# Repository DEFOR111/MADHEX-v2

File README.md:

# ***MADHEX-v2***
> ## the Fully open source 6 legged hexapod robot 

* Custom controller PCB
* Fully open-source
* great mechanics design with amortization
#### the 18DOF hexapod robot 

## the README include 
* Overwiew
* Features
* Electronics
* CAD
* firmware
* BOM

# Overview 
MadHex v2 is an open-source hexapod robot designed for people who wanna build their spider friend and learn building — CAD, PCB , and design  are all custom-made. This repository contains everything needed to reproduce the robot: CAD source and manufacturing files, PCB design and production files, bill of materials

Currently the project is in procces of building 

# Features

* Fully custom mechanical design , all parts are 3d printable
* custom control PCB : schematics , 4 layer of layout , kicad project , and manufactoring files
* 2 Full BOM files for both PCB and Robot
* great design with beatiful decisions

 # Electronics PCB 
 ### The schematics 

### the renders

Custom 4-layer control board 

**Key Features :**

* **MCU:** ESP32-S3-WROOM-1 — great wifi/bluetooth MCU 
* **IMU:** BNO055  — 9-DOF orientation for balancing
* **Power input:** XT60 connector - for battery connection 
* **Power protection:** low-side N-MOSFET reverse-polarity protection NTMFS5C404NL + SMBJ10CA TVS diode + 30A fuse
* **Regulation:** two TPS563201 buck converters: battery → 5.3V → Schottky → 5V rail → 3.3V
* **USB power path:** Schottky diodes keep USB and the battery side separated
* **Power monitoring:** INA226 current/voltage sensor (I2C) with a 2m shunt + analog voltage divider as backup 
* **USB-C:**  USB with USBLC6-2P6 ESD protection
* **Status LED:**  WS2812 RGB
* **Servo interface:** 2× independent half-duplex UART buses , 3 legs per bus — driving serial bus servos over a single data line per bus instead of  PWM channels
* **Connectors:** 6 3-pin leg connectors (J2–J7), one per leg makes the wiring a lot easier 

**Files:**
* Schematic: [download the schematics](Electronics/Hexapod%20PCB%202.pdf)
* Gerbers + drill files : [Download the manufactoring files](Electronics/manufactoring%20files.zip)
* BOM: [download the PCB BOM](BOM-PCB.csv)

**Board spec:**

| Spec | Value |
|---|---|
| Layers | 4 |
| MCU | ESP32-S3-WROOM-1 |
| Logic  | 3.3V |
| Peripheral  | 5V |
| Servo buses | 2× half-duplex UART (3 legs each) |
| Power input | XT60 |
| Current sensing | INA226 |

# CAD

Fully custom mechanical design, designed in autodesk Fusion every part is 3D-printable 

**values:**

| Spec | Value |
|---|---|
| size | 600 × 175 mm |
| DOF per leg | 3 (coxa – femur – tibia) |
| Total DOF | 18 |
| Coxa (axis to axis) | 45 mm |
| Femur (axis to axis) | 128 mm |
| Tibia (knee axis to foot tip) | 141.8 mm straight line, 168.5 mm along the curved part |
| Actuators | LX-16A serial bus servo, 17 kg·cm at 6V / 19.5 kg·cm at 7.4V (×18) |

Segment lengths were chosen using the servo torque  

**3D printing:**

| Spec | Value |
|---|---|
| Material | PETG |
| Total printed weight | ~878–950 g (all parts, with supports) |
| Parts | download [3d printing STL parts ](CAD/STL(3d%20printing%20parts)) |

PETG was chosen over PLA for better impact resistance sustained servo load — legs take repeated ground-impact stress during walking.

**Foot amortization (printed spring):**

Each foot includes a printed compliant spring element (PETG) acting as a passive shock absorber — it absorbs ground-impact impulse on footfall instead of transmitting it directly into the leg linkage/servo horn, reducing mechanical stress and jitter during walking.

**Files:**

| Format | Path | Use case |
|---|---|---|
| `.f3d` / `.f3z` | [autodesk fusion source file](CAD/source(f3d)) | Editable native Fusion source |
| `.step` | [full robot design universal file](CAD/step) | Full assembly + parts, universal format |
| `.stl` | [3d printing files](CAD/STL(3d%20printing%20parts)) | ready to slice |
| Renders | [photos of the CAD](CAD/renders) | Reference images |

Full parts list, printed vs. purchased components, and quantities: [see the main BOM](BOM%20main.csv)

# Bill of Materials

Two separate BOMs are provided — one for the full robot, one for the PCB only.

### Full Robot BOM

Full file: [see the full main BOM](BOM%20main.csv)

| Item | Qty | Description | Price |
|---|---|---|---|
| PCB | 1 | Custom PCB, UART servo controller — see [PCB BOM](BOM-PCB.csv) below | $50.10 |
| LX-16A | 18 | Serial bus UART servo, 17 kg·cm @6V / 19.5 kg·cm @7.4V | $252.00 |
| Battery | 1 | 6000mAh 2S, 7.4–8.4V, ≥30A discharge | $29.70 |
| Auto Fuse + holder | 1 | 30A safety fuse | $5.31 |
| XT60 | 1 | Pack of male/female connectors | $2.00 |
| Power wire | — | Silicone 14 AWG, battery → PCB | — |
| PETG | 900g | Filament for 3D-printed parts (min. 900g) | — |
| M3 screws | pack | Structural assembly | — |
| M3×5 inserts | pack | Heat-set inserts, structural assembly | — |
| M2 screws | pack | Servo mounting | — |
| Wires | pack | Electronics wiring | — |
| PCB manufacturing | 1 | Bare PCB fab, green solder mask | $14.00 |
| **Total** | | *incl. VAT, delivery, components* | **$420** |

### PCB BOM

Full file: [see the full PCB BOM](BOM-PCB.csv)

| Ref Des | Qty | Description | Value | Footprint | Price (unit) |
|---|---|---|---|---|---|
| C1, C2, C23, C24 | 4 | Electrolytic cap | 1000µF 16V | CP_Elec 10×10mm | $2.23 |
| C3, C4, C9, C10 | 4 | Ceramic cap | 10µF 25V | 0805 | $1.21 |
| C5, C6, C11, C14, C16, C18–C22, C25, C26 | 12 | Ceramic cap | 0.1µF 100V | 0805 | $0.91 |
| C7, C8, C12, C13, C15 | 5 | Ceramic cap | 22µF 25V | 0805 | $1.68 |
| C17 | 1 | Ceramic cap | 1µF 50V | 0805 | $1.08 |
| D1 | 1 | TVS diode, bidirectional | SMBJ10CA | SMB | $0.55 |
| D2 | 1 | RGB LED | WS2812B | PLCC-6 | $0.52 |
| D3, D4 | 2 | Schottky diode 3A 40V | SS34 | SMA | $0.70 |
| D5 | 1 | Zener diode 12V | BZT52C12 | SOD-123 | $0.56 |
| J1 | 1 | Battery connector | XT60-M, PCB mount | AMASS XT60-M | $0.38 |
| J2–J7 | 6 | Servo bus connector (leg1–leg6) | 3-pin 2.5mm JST XH | JST_XH_B3B | $0.55 |
| J8 | 1 | USB-C receptacle | USB 2.0, 16-pin | HRO TYPE-C-31-M-12 | $0.86 |
| L1 | 1 | Power inductor | 3.3µH | SRN4018 | $0.59 |
| L2 | 1 | Power inductor | 2.2µH | SRN4018 | $1.76 |
| Q1 | 1 | N-MOSFET, reverse polarity protection | NTMFS5C404NLT1G | DFN-5 5×6 | $2.62 |
| Q2, Q3 | 2 | NPN transistor, half-duplex | MMBT3904 | SOT-23 | $0.72 |
| R1, R3–R6, R14, R15, R18–R20, R22 | 11 | Resistor | 10k | 0805 | $0.45 |
| R2 | 1 | Resistor | 59k | 0805 | $0.41 |
| R7, R9 | 2 | Resistor | 33k | 0805 | $0.45 |
| R8, R28 | 2 | Resistor | 100k | 0805 | $0.45 |
| R10, R12, R24, R29 | 4 | Resistor | 1k | 0805 | $0.45 |
| R11, R13, R25, R26 | 4 | Resistor | 4.7k | 0805 | $0.45 |
| R16, R17 | 2 | Resistor | 5.1k | 0805 | $0.45 |
| R21 | 1 | Resistor | 330R | 0805 | $0.45 |
| R23 | 1 | Shunt resistor 2mΩ 1% 5W | Bourns CSS2H-2512K-2L00F | 2512 | $0.80 |
| SW2, SW3 | 2 | Tactile button | TS-1088 | SMD | $0.64 |
| U1, U2 | 2 | Buck converter | TPS563201 | SOT-23-6 | $0.78 |
| U3 | 1 | MCU module (8MB flash, no PSRAM) | ESP32-S3-WROOM-1-N8 | SMD module | $4.91 |
| U4 | 1 | ESD protection | USBLC6-2P6 | SOT-666 | $1.33 |
| U5 | 1 | 9-axis IMU | BNO055 | LGA-28 | $9.41 |
| U6 | 1 | Current/voltage monitor | INA226 | TSSOP-10 | $0.83 |
| **Total (per board)** | | *incl. LCSC + AliExpress delivery, 16% VAT, shipping* | | **$49.87** |

# Firmware

Written in C++ with PlatformIO (Arduino framework) for the ESP32-S3

**Features:**

* **Inverse kinematics** from the CAD joint points, with joint limits
* **Gaits:** ripple (default), tripod and wave
* **Movement:** forward, backward, sideways, turning in place, combined; adjustable body height
* **States:** sit, stand up, stand, walk, sit down, emergency stop
* **Safe startup:** servo output is off after power-up; when enabled, it reads every servo position and moves slowly to the sitting pose
* **Calibration:** trim and direction for each of the 18 servos
* **Safety:** low battery, servo overheating, emergency stop, stop on lost Wi-Fi link
* **Sensors:** INA226 current and voltage, BNO055 orientation, optional body leveling
* **Status LED:** a color for each robot state
* **Tests:** 200+ unit tests that run on a PC without hardware

**Pinout:**

| Function | GPIO |
|---|---|
| Servo bus 1 TX / RX (legs A, B, F) | 4 / 5 |
| Servo bus 2 TX / RX (legs C, D, E) | 17 / 18 |
| I2C SDA / SCL (INA226 0x40, BNO055 0x28) | 8 / 9 |
| Battery voltage (ADC) | 1 |
| WS2812 data | 7 |
| BNO055 reset / interrupt | 10 / 11 |
| USB D− / D+ | 19 / 20 |

**Build and flash** (VS Code + PlatformIO):

```
cd Firmware
pio test -e native        # unit tests on the PC
pio run -t upload         # flash the ESP32-S3 over USB-C
pio run -t uploadfs       # upload the web control page
```
a bit about the project history : i always wanted to make the hexapod but had no skills so 1 year passed i got pretty good skills in cad electronics and etc so now this project is real

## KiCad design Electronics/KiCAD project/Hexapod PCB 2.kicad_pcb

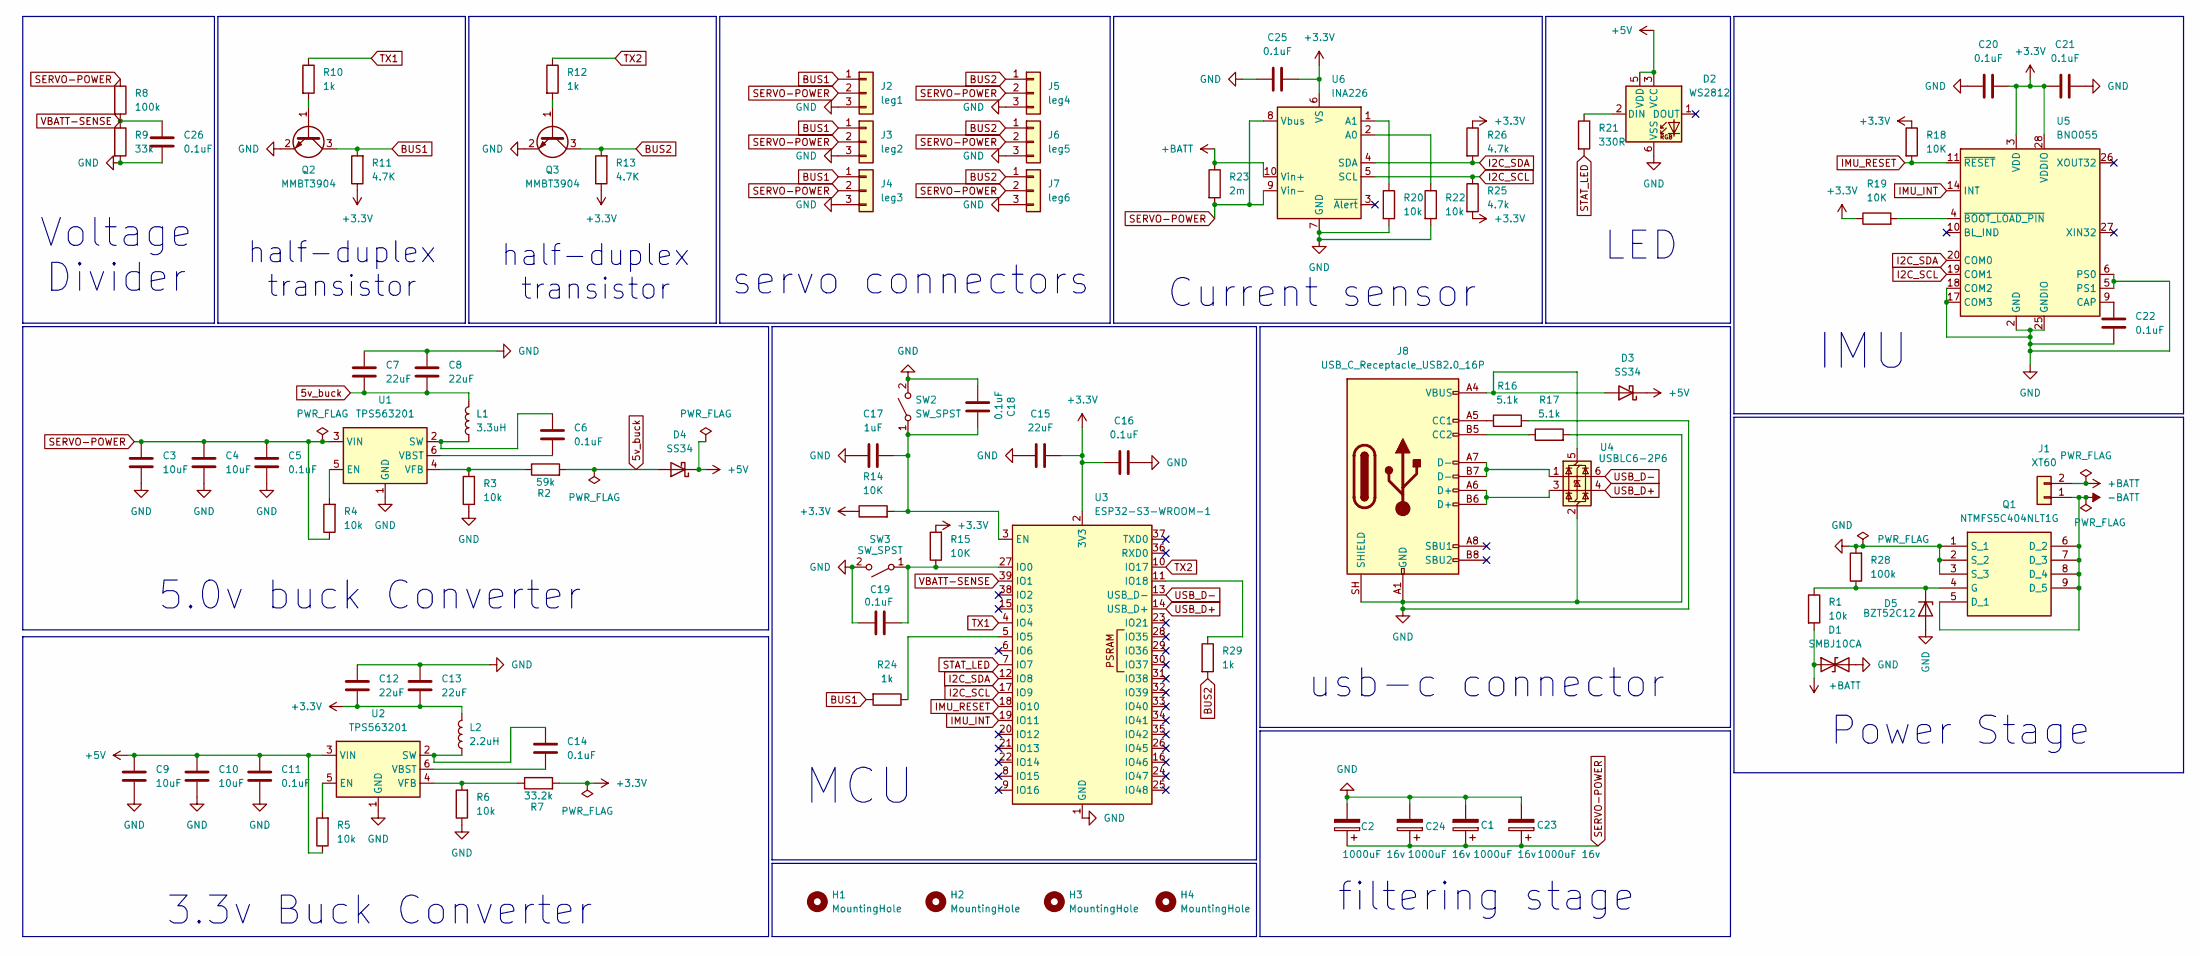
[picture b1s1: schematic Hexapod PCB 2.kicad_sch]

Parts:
C1, C2, C23, C24: 1000uF 16v; CP_Elec_10x10
C3, C4, C9, C10: 10uF; C_0805_2012Metric
C5, C6, C11, C14, C16, C18, C19, C20, C21, C22, C25, C26: 0.1uF; C_0805_2012Metric
C7, C8, C12, C13, C15: 22uF; C_0805_2012Metric
C17: 1uF; C_0805_2012Metric
D1: SMBJ10CA; D_SMB
D2: WS2812; LED_WS2812_PLCC6_5.0x5.0mm_P1.6mm
D3, D4: SS34; D_SMA
D5: BZT52C12; D_SOD-123
H1, H2, H3, H4: MountingHole; MountingHole_3.2mm_M3
J1: XT60; AMASS_XT60-M_1x02_P7.20mm_Vertical
J2: leg1; JST_XH_B3B-XH-A_1x03_P2.50mm_Vertical
J3: leg2; JST_XH_B3B-XH-A_1x03_P2.50mm_Vertical
J4: leg3; JST_XH_B3B-XH-A_1x03_P2.50mm_Vertical
J5: leg4; JST_XH_B3B-XH-A_1x03_P2.50mm_Vertical
J6: leg5; JST_XH_B3B-XH-A_1x03_P2.50mm_Vertical
J7: leg6; JST_XH_B3B-XH-A_1x03_P2.50mm_Vertical
J8: USB_C_Receptacle_USB2.0_16P; USB_C_Receptacle_HRO_TYPE-C-31-M-12
L1: 3.3uH; L_Bourns-SRN4018
L2: 2.2uH; L_Bourns-SRN4018
Q1: NTMFS5C404NLT1G; NTMFS4C022N; Mouser Part Number 863-NTMFS5C404NLT1G
Q2, Q3: MMBT3904; SOT-23
R1, R3, R4, R5, R6, R20, R22: 10k; R_0805_2012Metric
R2: 59k; R_0805_2012Metric
R7: 33.2k; R_0805_2012Metric
R8, R28: 100k; R_0805_2012Metric
R9: 33k; R_0805_2012Metric
R10, R12, R24, R29: 1k; R_0805_2012Metric
R11, R13: 4.7K; R_0805_2012Metric
R14, R15, R18, R19: 10K; R_0805_2012Metric
R16, R17: 5.1k; R_0805_2012Metric
R21: 330R; R_0805_2012Metric
R23: 2m; R_2512_6332Metric
R25, R26: 4.7k; R_0805_2012Metric
SW2, SW3: SW_SPST; SW_SPST_TS-1088-xR020
U1, U2: TPS563201; SOT-23-6
U3: ESP32-S3-WROOM-1
U4: USBLC6-2P6; SOT-666
U5: BNO055; LGA-28_5.2x3.8mm_P0.5mm
U6: INA226; TSSOP-10_3x3mm_P0.5mm

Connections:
5v_buck: C7.2, C8.2, D4.2 (A), L1.2, R2.2
+3.3V: C12.2, C13.2, C15.2, C16.1, C20.2, C21.1, C25.2, L2.2, R7.2, R11.1, R13.1, R14.1, R15.2, R18.1, R19.1, R25.2, R26.1, U3.2 (3V3), U5.3 (VDD), U5.28 (VDDIO), U6.6 (VS)
+5V: C9.1, C10.1, C11.1, D2.3 (VCC), D2.5 (VDD), D3.1 (K), D4.1 (K), R5.1, U2.3 (VIN)
+BATT: D1.1 (A1), J1.2, R1.2, R23.1, U6.10 (Vin+)
-BATT: J1.1, Q1.5 (D_1), Q1.6 (D_2), Q1.7 (D_3), Q1.8 (D_4), Q1.9 (D_5)
BUS1: J2.1, J3.1, J4.1, Q2.3 (C), R11.2, R24.2
BUS2: J5.1, J6.1, J7.1, Q3.3 (C), R13.2, R29.2
GND: C1.2, C2.2, C3.2, C4.2, C5.2, C7.1, C8.1, C9.2, C10.2, C11.2, C12.1, C13.1, C15.1, C16.2, C17.2, C18.2, C19.2, C20.1, C21.2, C22.1, C23.2, C24.2, C25.1, C26.2, D1.2 (A2), D2.6 (VSS), D5.2 (A), J2.3, J3.3, J4.3, J5.3, J6.3, J7.3, J8.A1 (GND), J8.A12 (GND), J8.B1 (GND), J8.B12 (GND), J8.SH (SHIELD), Q1.1 (S_1), Q1.2 (S_2), Q1.3 (S_3), Q2.2 (E), Q3.2 (E), R3.1, R6.1, R9.2, R16.2, R17.2, R20.2, R22.2, R28.2, SW2.2 (B), SW3.2 (B), U1.1 (GND), U2.1 (GND), U3.1 (GND), U3.40 (GND), U3.41 (GND), U4.2 (GND), U5.2 (GND), U5.5 (PS1), U5.6 (PS0), U5.17 (COM3), U5.18 (COM2), U5.25 (GNDIO), U6.7 (GND)
I2C_SCL: R25.1, U3.17 (IO9), U5.19 (COM1), U6.5 (SCL)
I2C_SDA: R26.2, U3.12 (IO8), U5.20 (COM0), U6.4 (SDA)
IMU_INT: U3.19 (IO11), U5.14 (INT)
IMU_RESET: R18.2, U3.18 (IO10), U5.11 (~RESET)
unnamed: D2.2 (DIN), R21.1
unnamed: D3.2 (A), J8.A4 (VBUS), J8.A9 (VBUS), J8.B4 (VBUS), J8.B9 (VBUS), U4.5 (VBUS)
unnamed: D5.1 (K), Q1.4 (G), R1.1, R28.1
unnamed: J8.A5 (CC1), R16.1
unnamed: J8.B5 (CC2), R17.1
unnamed: J8.A6 (D+), J8.B6 (D+), U4.3 (I/O2)
unnamed: J8.A7 (D-), J8.B7 (D-), U4.1 (I/O1)
unnamed: Q2.1 (B), R10.2
unnamed: Q3.1 (B), R12.2
unnamed: C17.1, C18.1, R14.2, SW2.1 (A), U3.3 (EN)
unnamed: C19.1, R15.1, SW3.1 (A), U3.27 (IO0)
unnamed: R4.2, U1.5 (EN)
unnamed: C6.2, L1.1, U1.2 (SW)
unnamed: C6.1, U1.6 (VBST)
unnamed: R2.1, R3.2, U1.4 (VFB)
unnamed: R5.2, U2.5 (EN)
unnamed: C14.2, L2.1, U2.2 (SW)
unnamed: C14.1, U2.6 (VBST)
unnamed: R6.2, R7.1, U2.4 (VFB)
unnamed: R24.1, U3.5 (IO5)
unnamed: R29.1, U3.11 (IO18)
unnamed: C22.2, U5.9 (CAP)
unnamed: R19.2, U5.4 (~BOOT_LOAD_PIN)
unnamed: R22.1, U6.2 (A0)
unnamed: R20.1, U6.1 (A1)
SERVO-POWER: C1.1, C2.1, C3.1, C4.1, C5.1, C23.1, C24.1, J2.2, J3.2, J4.2, J5.2, J6.2, J7.2, R4.1, R8.1, R23.2, U1.3 (VIN), U6.8 (Vbus), U6.9 (Vin-)
STAT_LED: R21.2, U3.7 (IO7)
TX1: R10.1, U3.4 (IO4)
TX2: R12.1, U3.10 (IO17)
USB_D+: U3.14 (USB_D+), U4.4 (I/O2)
USB_D-: U3.13 (USB_D-), U4.6 (I/O1)
VBATT-SENSE: C26.1, R8.2, R9.1, U3.39 (IO1)

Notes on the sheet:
Current sensor
filtering stage
Power Stage
MCU
Voltage Divider
IMU
LED
servo connectors
usb-c connector
5.0v buck Converter
half-duplex transistor
3.3v Buck Converter

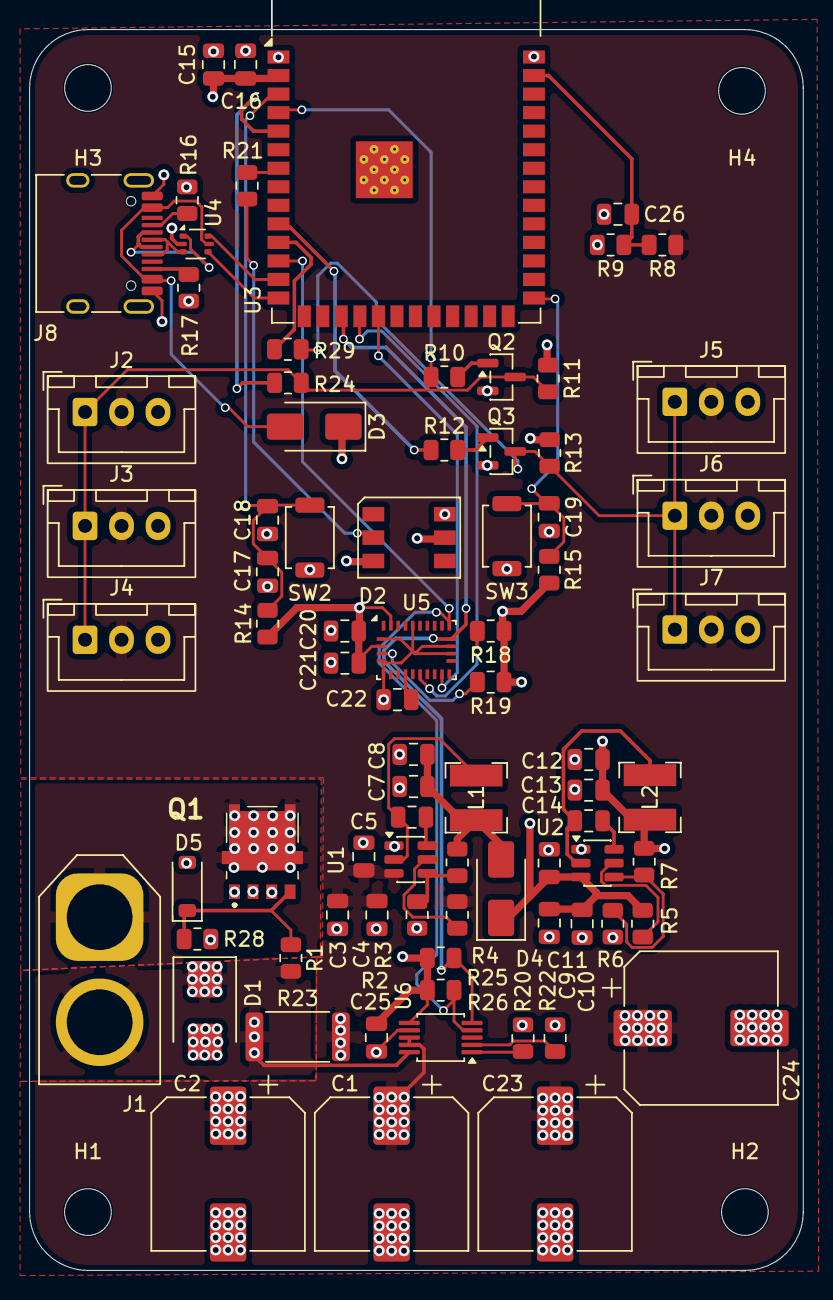
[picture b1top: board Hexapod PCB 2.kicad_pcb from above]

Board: 4 copper layers, 53.0 x 85.0 mm, 84 parts (0 on the bottom side), 44 nets.

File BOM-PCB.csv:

Hexapod Controller — BOM,,,,,,,
Qty (boards):,,,,,,,
,,,,,,,
Ref Des,Qty/bd,Total Qty,Description,Value,Footprint,link,price
"C1,C2,C23,C24",4,10,"Cap, electrolytic",1000uF 16V,CP_Elec 10x10mm,https://aliexpress.ru/item/1005002964957462.html?spm=a2g2w.c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,2.23$
"C3,C4,C9,C10",4,100,Cap ceramic,10uF 25v,805,https://aliexpress.ru/item/1005009339427569.html?spm=a2g2w.c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,1.21$
"C5,C6,C11,C14,C16,C18,C19,C20,C21,C22,C25,C26",12,100,Cap ceramic,0.1uF 100v,805,https://aliexpress.ru/item/1005009339427569.html?spm=a2g2w.c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,0.91$
"C7,C8,C12,C13,C15",5,50,Cap ceramic,22uF  25v,805,https://aliexpress.ru/item/1005008523091680.html?sku_id=1200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,1.68$
C17,1,100,Cap ceramic,1uF 50v,805,https://aliexpress.ru/item/1005009339427569.html?spm=a2g2w.c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,1.08$
D1,1,5,TVS diode bidirectional,SMBJ10CA,SMB,https://www.lcsc.com/product-detail/C83278.html?s_z=n_q_smbj10ca,0.55$
D2,1,5,RGB LED,WS2812B,PLCC-6 5.0x5.0mm P1.6mm,https://www.lcsc.com/product-detail/C114586.html?s_z=n_q_t_W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,0.52$
"D3,D4",2,10,Schottky diode 3A 40V,SS34,SMA,https://www.lcsc.com/product-detail/C8678.html?s_z=n_q_x_ss3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,0.7$
D5,1,10,Zener diode 12V,BZT52C12,SOD-123,https://www.lcsc.com/product-detail/C668891.html?s_z=n_q_bzt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,0.56$
J1,1,0,Battery connector,XT60-M PCB mount,AMASS XT60-M 1x02 P7.20mm Vertical,https://www.lcsc.com/product-detail/C5334533.html?spm=wm.gwc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,0.38$
J2-J7,6,0,Servo bus connector leg1-leg6,3-pin 2.5mm (JST XH),JST_XH_B3B-XH-A_1x03_P2.50mm_Vertical,https://www.lcsc.com/product-detail/C144394.html?s_z=n_q_C14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,0.55$
J8,1,0,USB-C receptacle,USB2.0 16-pin,HRO TYPE-C-31-M-12,https://www.lcsc.com/product-detail/C165948.html?s_z=n_q_C16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,0.86$
L1,1,0,Power inductor,3.3uH,SRN4018,https://www.lcsc.com/product-detail/C19947635.html?s_z=n_q_S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,0.59$
L2,1,5,Power inductor,2.2uH,SRN4018,https://www.lcsc.com/product-detail/C913207.html,1.76$
Q1,1,2,N-MOSFET reverse polarity protection,NTMFS5C404NLT1G,DFN-5 5x6 (SO-8FL),https://www.lcsc.com/product-detail/C604432.html,2.62$
"Q2,Q3",2,20,NPN transistor half-duplex,MMBT3904,SOT-23,https://www.lcsc.com/product-detail/C242260.html?s_z=n_q_mmb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,0.72$
"R1,R3,R4,R5,R6,R14,R15,R18,R19,R20,R22",11,100,Resistor,10k,805,https://aliexpress.ru/item/1005009887091465.html?sku_id=1200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,0.45$
R2,1,100,Resistor ,59k,805,https://aliexpress.ru/item/1005009887091465.html?sku_id=1200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,0.41$
"R8,R28",2,100,Resistor ,100k,805,https://aliexpress.ru/item/1005009887091465.html?sku_id=1200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,0.45$
"R9,R7",1,100,Resistor ,33k,805,https://aliexpress.ru/item/1005009887091465.html?sku_id=1200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,0.45$
"R10,R12,R24,R29",4,100,Resistor,1k,805,https://aliexpress.ru/item/1005009887091465.html?sku_id=1200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,0.45$
"R11,R13,R25,R26",4,100,Resistor,4.7k,805,https://aliexpress.ru/item/1005009887091465.html?sku_id=1200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,0.45$
"R16,R17",2,100,Resistor,5.1k,805,https://aliexpress.ru/item/1005009887091465.html?sku_id=1200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,0.45$
R21,1,100,Resistor,330R,805,https://aliexpress.ru/item/1005009887091465.html?sku_id=1200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,0.45$
R23,1,5,Shunt resistor 2 mOhm 1% 5W,CSS2H-2512K-2L00F,2512,bourns css2h-2512k-2l00f - Chip Resistor - Surface Mount,0.80$
"SW2,SW3",2,10,Tactile button,TS-1088,SMD,https://www.lcsc.com/product-detail/C455280.html?s_z=n_q_ts-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,0.64$
"U1,U2",2,10,"Buck converter
",TPS563201,SOT-23-6,https://www.lcsc.com/product-detail/C116592.html?s_z=n_q_C11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,0.78$
U3,1,0,"MCU module (8MB flash, no PSRAM)",ESP32-S3-WROOM-1-N8,SMD module,https://www.lcsc.com/product-detail/C2913198.html?s_z=n_q_C2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  ,4.91$
U4,1,0,ESD protection,USBLC6-2P6,SOT-666,https://www.lcsc.com/product-detail/C15999.html?s_z=n_q_c159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,1.33$
U5,1,0,9-axis IMU,BNO055,LGA-28 3.8x5.2mm,https://www.lcsc.com/product-detail/C93216.html?s_z=n_q_C932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,9.41$
U6,1,0,Current/voltage monitor,INA226,TSSOP-10,https://www.lcsc.com/product-detail/C49851.html?s_z=n_q_C498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,0.83$
,,,,,LCSC+ALIEXPRESS+DELIVERY+16% VAT+SHIPPING,,TOTAL: 49.87$

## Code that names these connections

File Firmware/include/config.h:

#pragma once

#include <stdint.h>
#include "mathx.h"

struct JointLimits {
    float minDeg;
    float maxDeg;
};

struct LegConfig {
    const char *name;
    const char *position;
    Vec3 p1;
    Vec3 p2;
    Vec3 p3;
    Vec3 p4;
    JointLimits coxa;
    JointLimits femur;
    JointLimits tibia;
};

const JointLimits COXA_LIMITS  = {  -50.0,  50.0 };
const JointLimits FEMUR_LIMITS = {  -90.0,  90.0 };
const JointLimits TIBIA_LIMITS = { -110.0, 110.0 };

const int LEG_COUNT = 6;

const LegConfig LEGS[LEG_COUNT] = {
    {
        "A", "right middle",
        {  -96.0,    0.0, 60.0 },
        { -141.0,    0.0, 60.0 },
        { -269.0,    0.0, 60.0 },
        { -405.0,    0.0, 20.0 },
        COXA_LIMITS, FEMUR_LIMITS, TIBIA_LIMITS
    },
    {
        "B", "right rear",
        {  -88.0,   81.5, 60.0 },
        { -126.5,  103.5, 60.0 },
        { -236.5,  167.0, 60.0 },
        { -355.0,  235.0, 20.0 },
        COXA_LIMITS, FEMUR_LIMITS, TIBIA_LIMITS
    },
    {
        "C", "left rear",
        {   88.0,   81.5, 60.0 },
        {  126.5,  103.5, 60.0 },
        {  236.5,  167.0, 60.0 },
        {  355.0,  235.0, 20.0 },
        COXA_LIMITS, FEMUR_LIMITS, TIBIA_LIMITS
    },
    {
        "D", "left middle",
        {   96.0,    0.0, 60.0 },
        {  141.0,    0.0, 60.0 },
        {  269.0,    0.0, 60.0 },
        {  405.0,    0.0, 20.0 },
        COXA_LIMITS, FEMUR_LIMITS, TIBIA_LIMITS
    },
    {
        "E", "left front",
        {   88.0,  -81.5, 60.0 },
        {  126.5, -103.5, 60.0 },
        {  236.5, -167.0, 60.0 },
        {  355.0, -235.0, 20.0 },
        COXA_LIMITS, FEMUR_LIMITS, TIBIA_LIMITS
    },
    {
        "F", "right front",
        {  -88.0,  -81.5, 60.0 },
        { -126.5, -103.5, 60.0 },
        { -236.5, -167.0, 60.0 },
        { -355.0, -235.0, 20.0 },
        COXA_LIMITS, FEMUR_LIMITS, TIBIA_LIMITS
    },
};

const int REFERENCE_LEG = 0;

const float LENGTH_WARNING_MM = 1.0;

const Vec3 STAND_FOOT_A = { -305.0, 0.0, 0.0 };

const float BODY_UNDERSIDE_Z = 30.0;

const float GAIT_STRIDE_MM = 80.0;
const float GAIT_LIFT_MM = 25.0;
const float GAIT_SWING_S = 0.5;
const float GAIT_RAMP_S = 1.0;
const float GAIT_TURN_DEG = 14.0;
const float GAIT_LIFT_FADE = 0.25;

const int SERVO_BUS1_TX_PIN = 4;
const int SERVO_BUS1_RX_PIN = 5;
const int SERVO_BUS2_TX_PIN = 17;
const int SERVO_BUS2_RX_PIN = 18;
const unsigned long SERVO_BAUD = 115200;

const uint8_t SERVO_ID[LEG_COUNT][3] = {
    {  1,  2,  3 },
    {  4,  5,  6 },
    {  7,  8,  9 },
    { 10, 11, 12 },
    { 13, 14, 15 },
    { 16, 17, 18 },
};

const int SERVO_BUS_OF_LEG[LEG_COUNT] = { 1, 1, 2, 2, 2, 1 };

const unsigned long SERVO_REPLY_TIMEOUT_MS = 20;
const unsigned long SERVO_ID_VERIFY_TIMEOUT_MS = 100;
const int SERVO_TEST_MOVE_MS = 2000;

const float TRIM_LIMIT_DEG = 30.0;
const int CALIBRATION_MOVE_MS = 1000;
const int TRIM_MOVE_MS = 200;

const unsigned long SAFETY_CHECK_PERIOD_MS = 1000;
const int SAFETY_LOW_VOLTAGE_MV = 6600;
const int SAFETY_LOW_VOLTAGE_COUNT = 2;
const int SAFETY_MAX_TEMP_C = 70;
const unsigned long SAFETY_REPLY_TIMEOUT_MS = 10;

const int I2C_SDA_PIN = 8;
const int I2C_SCL_PIN = 9;
const unsigned long I2C_CLOCK_HZ = 400000;

const uint8_t INA226_ADDRESS = 0x40;
const float INA226_SHUNT_OHM = 0.002;
const float INA226_CURRENT_LSB_A = 0.001;
const int INA226_AVG_CODE = 2;
const int INA226_BUS_CT_CODE = 4;
const int INA226_SHUNT_CT_CODE = 4;
const unsigned long POWER_READ_PERIOD_MS = 100;

const int BATTERY_NOT_CONNECTED_MV = 1000;
const int BATTERY_CRITICAL_MV = 6400;
const int BATTERY_LOW_MV = 6800;
const int BATTERY_HYSTERESIS_MV = 200;

const uint8_t IMU_ADDRESS = 0x28;
const int IMU_RESET_PIN = 10;
const int IMU_INT_PIN = 11;
const unsigned long IMU_BOOT_TIMEOUT_MS = 1000;
const unsigned long IMU_READ_PERIOD_MS = 20;

const int IMU_AXIS_MAP[3] = {
    1,
    2,
    3,
};
const float IMU_HEADING_OFFSET_DEG = 0.0;

const char WIFI_AP_SSID[] = "hexapod";
const char WIFI_AP_PASSWORD[] = "hexapod123";
const unsigned long WEB_LINK_TIMEOUT_MS = 500;
const unsigned long WEB_STATUS_PERIOD_MS = 200;
const int WEB_MAX_CLIENTS = 2;

const float LEVEL_MAX_DEG = 6.0;
const float LEVEL_GAIN_PER_S = 1.0;
const float LEVEL_MAX_RATE_DEG_S = 5.0;
const float LEVEL_FILTER_S = 0.3;
const float LEVEL_DEADBAND_DEG = 0.5;

const int VBATT_ADC_PIN = 1;
const float VBATT_DIVIDER_TOP_OHM = 100000.0;
const float VBATT_DIVIDER_BOTTOM_OHM = 33000.0;

const float HEIGHT_CHANGE_S = 1.5;

const float STAND_HEIGHT_MIN_MM = -20.0;
const float STAND_HEIGHT_MAX_MM = 30.0;
const float STAND_HEIGHT_RATE_MM_S = 20.0;

const unsigned long UPDATE_PERIOD_MS = 20;

const float SERVO_STARTUP_MOVE_S = 2.5;

const int STATUS_LED_PIN = 7;
const uint8_t STATUS_LED_BRIGHTNESS = 40;
const unsigned long LED_BLINK_SLOW_MS = 1000;
const unsigned long LED_BLINK_FAST_MS = 400;
const unsigned long LED_WHITE_PERIOD_MS = 2000;
const unsigned long LED_WHITE_FLASH_MS = 100;
